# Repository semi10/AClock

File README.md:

AClock - Dot Matrix Display Information Board
Based on ATmega328P (Arduino)

Main Components:
Bicolor Red & Green LED 5mm Dot Matrix Display: http://store.sure-electronics.com/led/led-display/de-dp14211
RTC DS1307: http://datasheets.maximintegrated.com/en/ds/DS1307.pdf
EEPROM 24LC256: https://www.sparkfun.com/products/525
Humidity and Temperature Sensor RHT03: https://www.sparkfun.com/products/10167

Some Features:

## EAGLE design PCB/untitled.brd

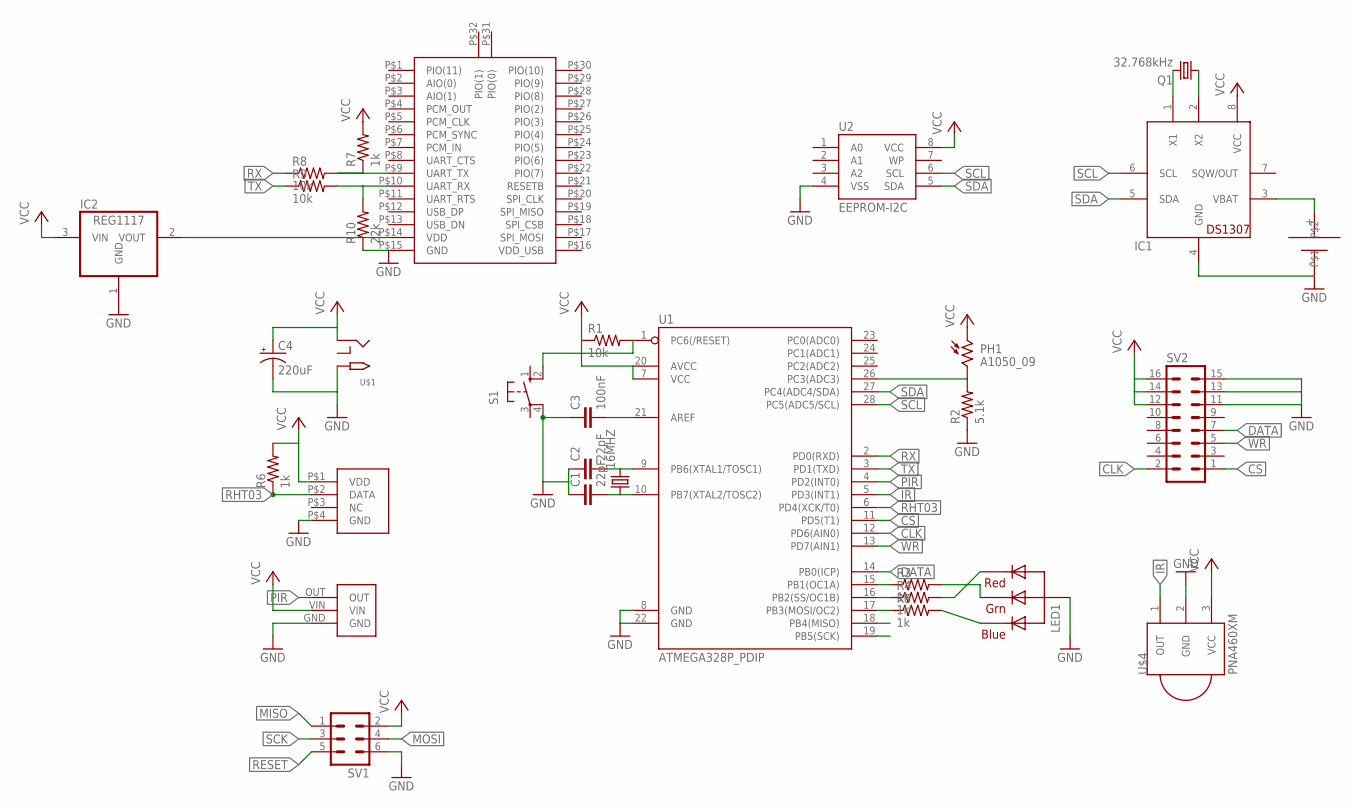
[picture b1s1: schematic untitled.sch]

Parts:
16MHZ: CRYSTALHC49U-H; HC49U-H
C1, C2: 22pF; C025-024X044
C3: 100nF; C025-024X044
C4: 220uF; E3,5-8
IC1: DS1307; DIL08
IC2: REG1117; SOT223
LED1: RGBLED_CA-5MM; LED5MMRGB
PH1: A1050_09; T0-46-A10XX
Q1: 32.768kHz; TC38H
R1, R8, R9: 10k; 0207/10
R2: 5.1k; 0207/10
R3, R4, R5, R6, R7: 1k; 0207/10
R10: 22k; 0207/10
S1: 10-XX; B3F-10XX
SV1: ML6
SV2: ML16
U1: ATMEGA328P_PDIP; DIL28-3
U2: EEPROM-I2C; DIL08
U$1: 2.1MMJACK; 2.1MMJACK_BREADBOARD
U$2: RHT03THROUGH_HOLE; RHT03
U$3: PIR_PM-6; PIR_THROUGHHOLE
U$4: PNA460XM
U$5: CR2032; CR2032-THM
U$6: BTM-182

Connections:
CLK: SV2.2, U1.12 (PD6(AIN0))
CS: SV2.1, U1.11 (PD5(T1))
DATA: SV2.7, U1.14 (PB0(ICP))
GND: C1.1, C2.1, C3.1, C4.-, IC1.4 (GND), IC2.1 (GND), LED1.2 (VCC), R2.1, R10.1, S1.4 (P1), SV1.6, SV2.11, SV2.13, SV2.15, U1.8 (GND), U1.22 (GND), U2.4 (VSS), U$1.GND (TIP), U$2.P$4 (GND), U$3.GND, U$4.2 (GND), U$5.-, U$6.P$15 (GND)
IR: U1.5 (PD3(INT1)), U$4.1 (OUT)
MISO: SV1.1, U1.18 (PB4(MISO))
MOSI: R5.1, SV1.4, U1.17 (PB3(MOSI/OC2))
unnamed: 16MHZ.1, C1.2, U1.10 (PB7(XTAL2/TOSC2))
unnamed: 16MHZ.2, C2.2, U1.9 (PB6(XTAL1/TOSC1))
unnamed: C3.2, U1.21 (AREF)
unnamed: R4.1, U1.16 (PB2(SS/OC1B))
unnamed: R3.1, U1.15 (PB1(OC1A))
unnamed: PH1.2, R2.2, U1.26 (PC3(ADC3))
unnamed: IC1.3 (VBAT), U$5.+
unnamed: IC2.2 (VOUT), U$6.P$14 (VDD)
unnamed: LED1.1 (RED), R4.2
unnamed: LED1.3 (GREEN), R3.2
unnamed: LED1.4 (BLUE), R5.2
unnamed: IC1.1 (X1), Q1.2
unnamed: IC1.2 (X2), Q1.1
unnamed: R7.1, R8.2, U$6.P$9 (UART_TX)
unnamed: R9.2, R10.2, U$6.P$10 (UART_RX)
PIR: U1.4 (PD2(INT0)), U$3.OUT
RESET: R1.2, S1.2 (S1), SV1.5, U1.1 (PC6(/RESET))
RHT03: R6.1, U1.6 (PD4(XCK/T0)), U$2.P$2 (DATA)
RX: R8.1, U1.2 (PD0(RXD))
SCK: SV1.3, U1.19 (PB5(SCK))
SCL: IC1.6 (SCL), U1.28 (PC5(ADC5/SCL)), U2.6 (SCL)
SDA: IC1.5 (SDA), U1.27 (PC4(ADC4/SDA)), U2.5 (SDA)
TX: R9.1, U1.3 (PD1(TXD))
VCC: C4.+, IC1.8 (VCC), IC2.3 (VIN), PH1.1, R1.1, R6.2, R7.2, SV1.2, SV2.12, SV2.14, SV2.16, U1.7 (VCC), U1.20 (AVCC), U2.8 (VCC), U$1.PWR (RING), U$2.P$1 (VDD), U$3.VIN, U$4.3 (VCC)
WR: SV2.5, U1.13 (PD7(AIN1))

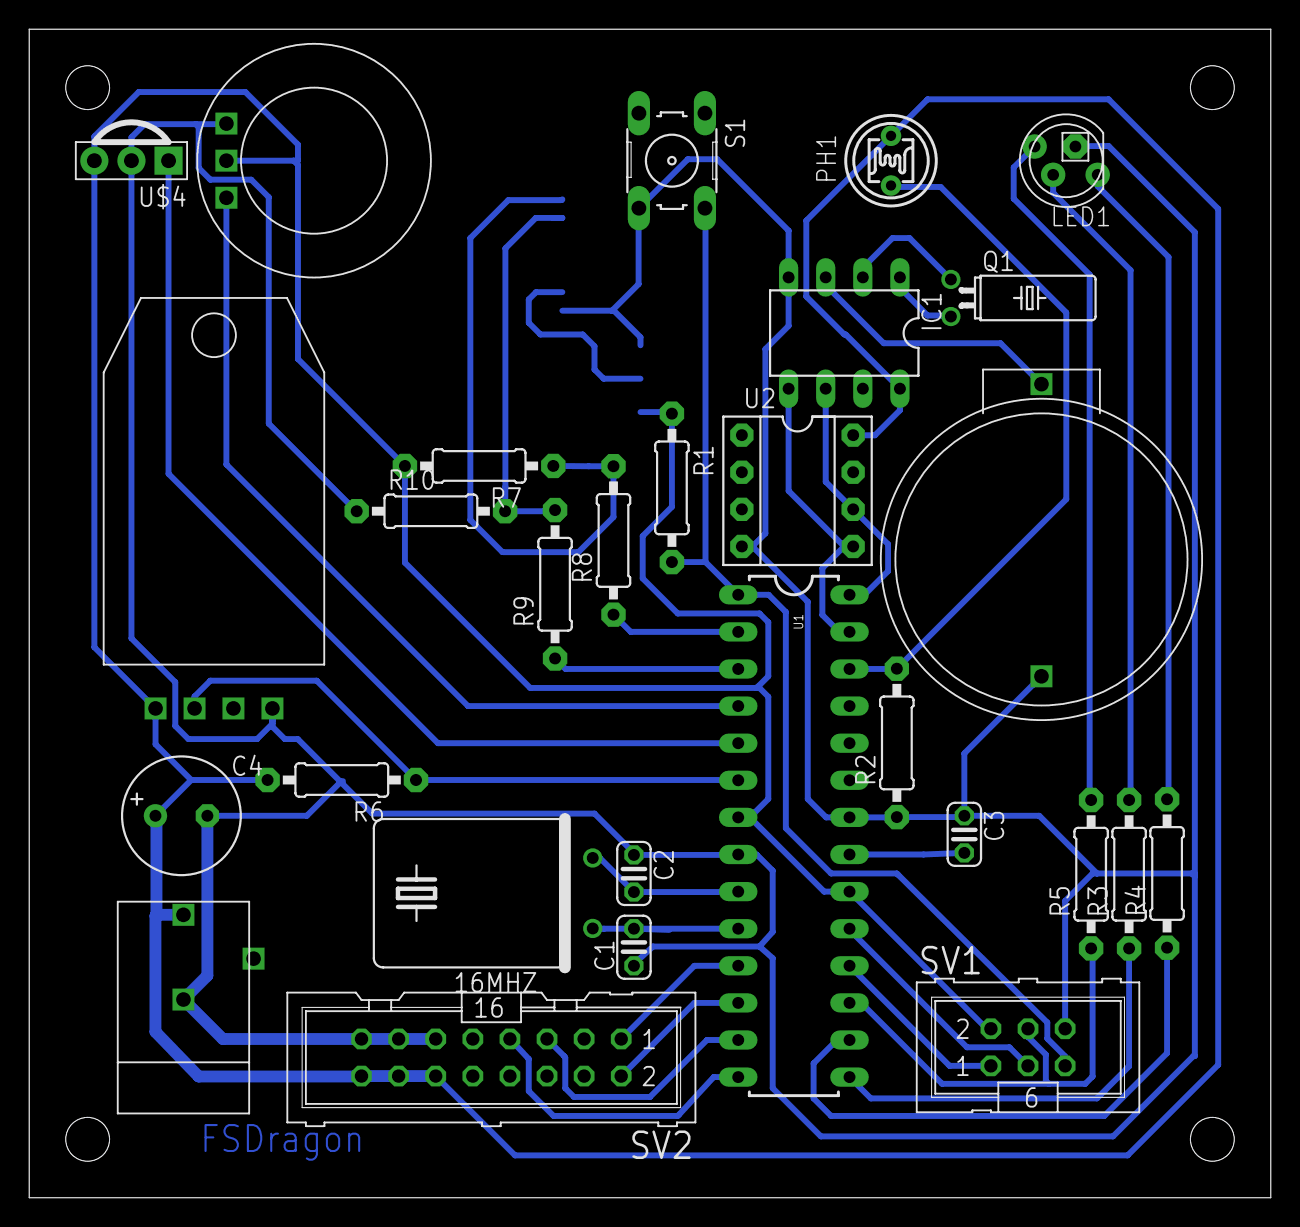
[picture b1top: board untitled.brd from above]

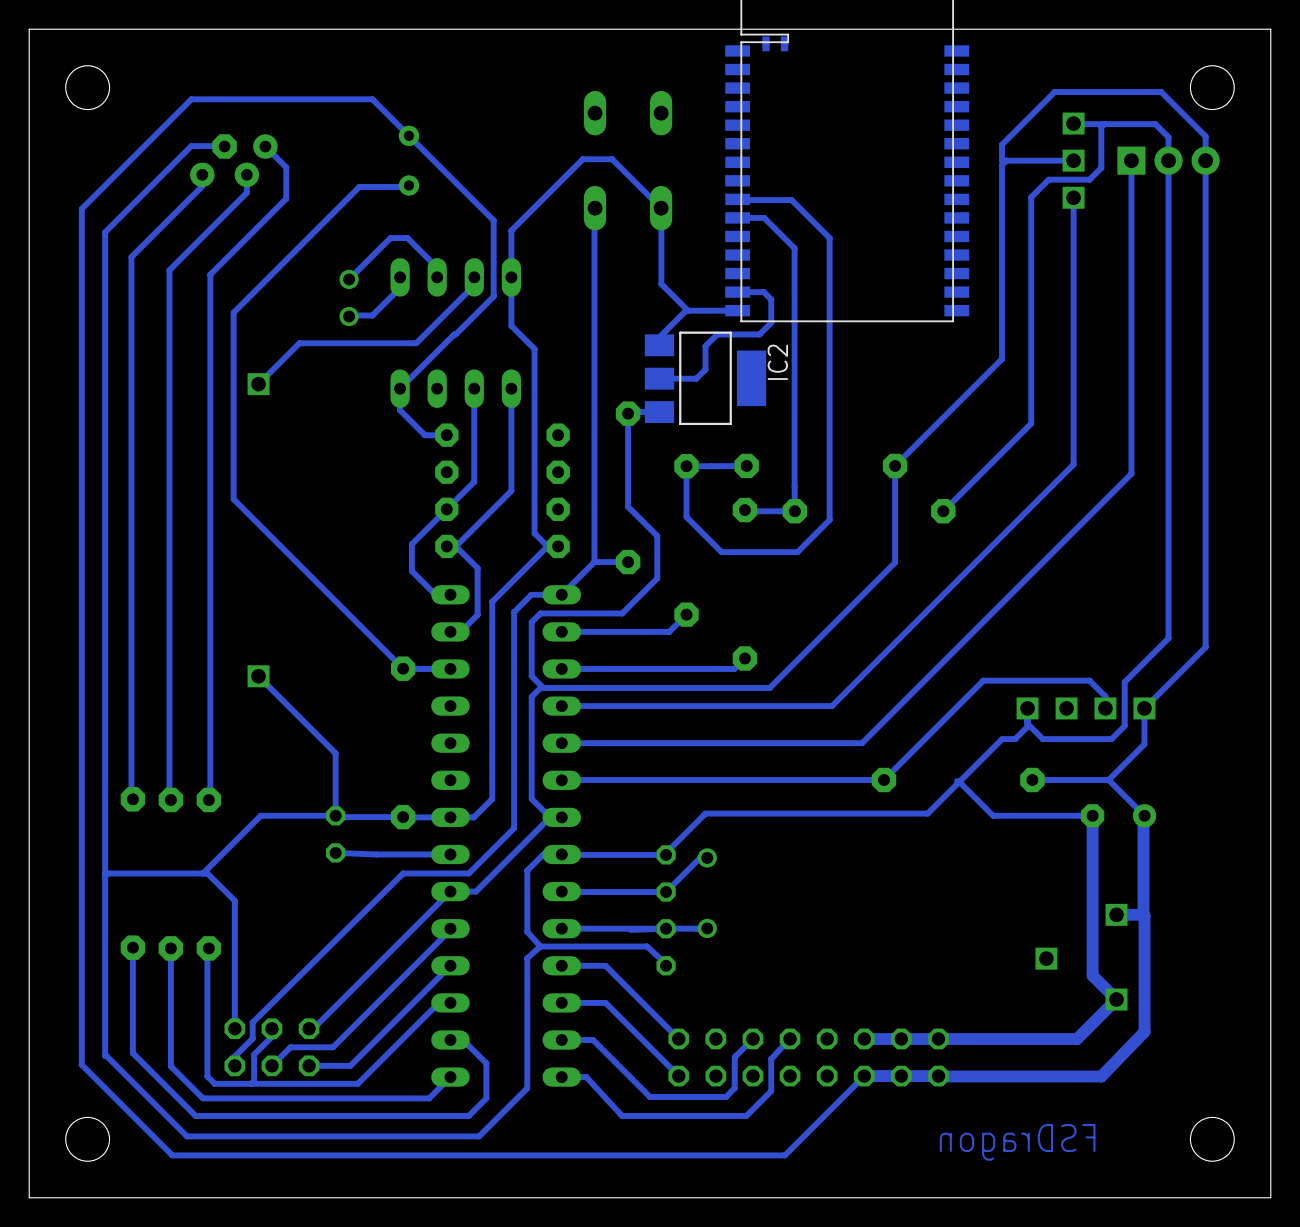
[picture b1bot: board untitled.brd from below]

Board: 1 copper layer, 85.0 x 80.0 mm, 31 parts (2 on the bottom side), 32 nets.

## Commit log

2013-07-28 Start
2013-07-30 Improved clock error representation
2015-06-03 Start from scratch
2015-06-11 Speed
2015-06-20 IR receiver + Temperature & Humidity data logger + Ambient light sensor
2015-09-08 PCB development & minor code updates
2015-11-28 Eagle files add
2016-07-09 Print mechanism changed
2016-10-03 Progressbar added
2017-11-03 IR Library improved

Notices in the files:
parts and their libraries:
SparkFun-DigitalIC: Licensing: Creative Commons ShareAlike 4.0 International - https://creativecommons.org/licenses/by-sa/4.0
